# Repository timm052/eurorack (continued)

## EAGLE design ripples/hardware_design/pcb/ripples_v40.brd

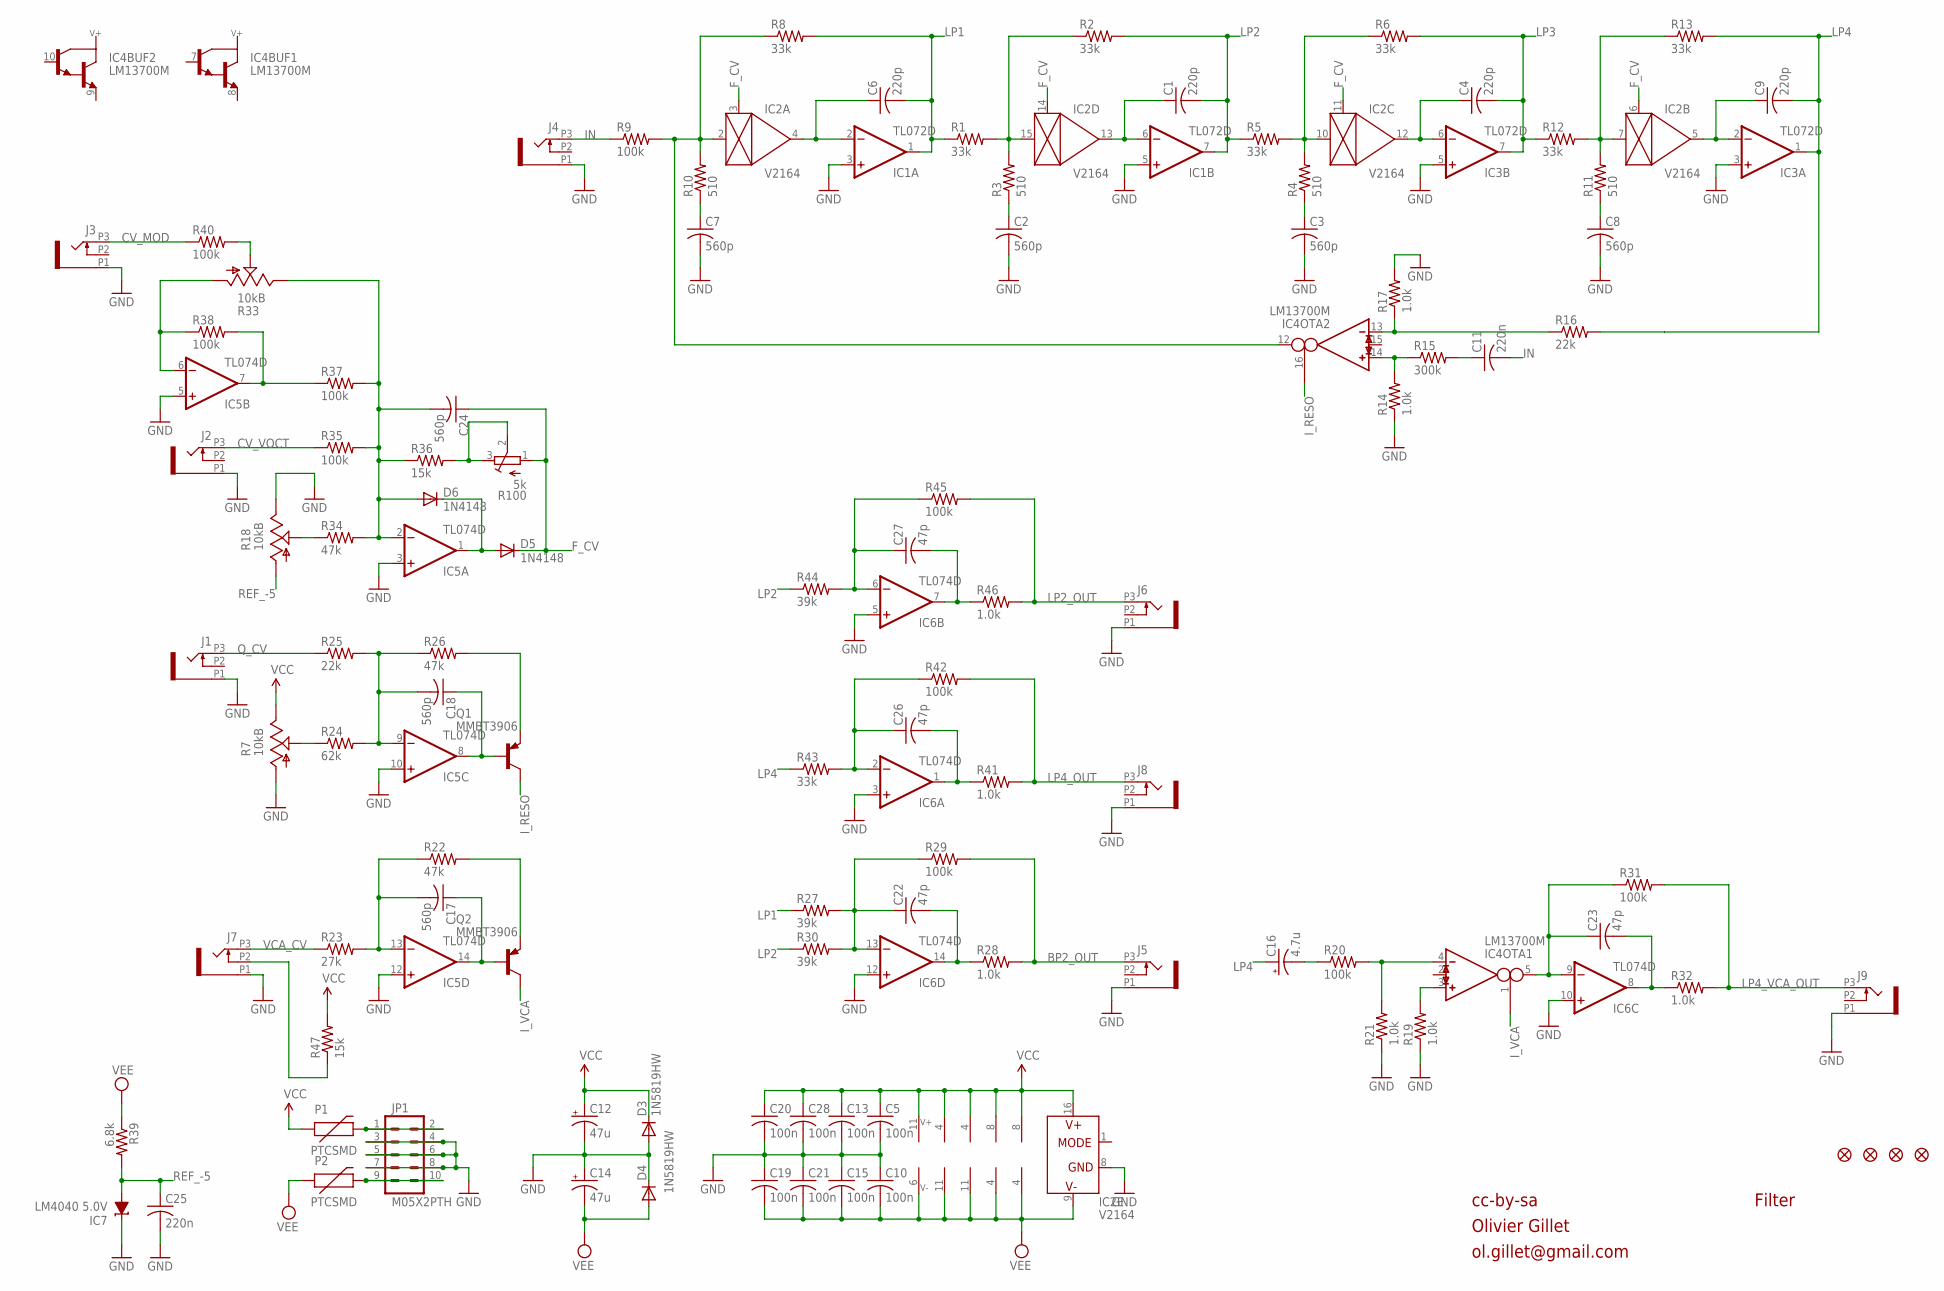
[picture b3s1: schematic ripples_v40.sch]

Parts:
C1, C4, C6, C9: 220p; C0603
C2, C3, C7, C8, C17, C18, C24: 560p; C0603
C5, C10, C13, C15, C19, C20, C21, C28: 100n; C0603
C11, C25: 220n; C0603
C12, C14: 47u; PANASONIC_D
C16: 4.7u; PANASONIC_B
C22, C23, C26, C27: 47p; C0603
D3, D4: 1N5819HW; SOD123
D5, D6: 1N4148; SOD323-W
F1, F2, F3, F4: FIDUCIAL1X2; FIDUCIAL-1X2
IC1, IC3: TL072D; SO08
IC2: V2164; SOIC16N
IC4: LM13700M; SO16
IC5, IC6: TL074D; SO14
IC7: LM4040 5.0V; DBZ_R-PDSO-G3
J1, J2, J3, J4, J5, J6, J7, J8, J9: PJ301_THONKICONN6; WQP_PJ_301M6
JP1: M05X2PTH; AVR_ICSP
P1, P2: PTCSMD; PTC-1206
Q1, Q2: MMBT3906; SOT23-BEC
R1, R2, R5, R6, R8, R12, R13, R43: 33k; R0603
R3, R4, R10, R11: 510; R0603
R7, R18, R33: 10kB; ALPS_POT_VERTICAL_PS
R9, R20, R29, R31, R35, R37, R38, R40, R42, R45: 100k; R0603
R14, R17, R19, R21, R28, R32, R41, R46: 1.0k; R0603
R15: 300k; R0603
R16, R25: 22k; R0603
R22, R26, R34: 47k; R0603
R23: 27k; R0603
R24: 62k; R0603
R27, R30, R44: 39k; R0603
R36, R47: 15k; R0603
R39: 6.8k; R0603
R100: 5k; RTRIM3296X

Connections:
BP2_OUT: J5.P3 (3), R28.2, R29.2
CV_F_POT: R18.P$2 (S), R34.1
CV_MOD: J3.P3 (3), R40.1
CV_VOCT: J2.P3 (3), R35.1
F_CV: C24.1, D5.C, IC2.3 (CTRL), IC2.6 (CTRL), IC2.11 (CTRL), IC2.14 (CTRL), R100.1 (E)
GND: C2.2, C3.2, C5.2, C7.2, C8.2, C10.1, C12.-, C13.2, C14.+, C15.1, C19.1, C20.2, C21.1, C25.2, C28.2, D3.A, D4.C, IC1.3 (+IN), IC1.5 (+IN), IC2.8 (GND), IC3.3 (+IN), IC3.5 (+IN), IC5.3 (+IN), IC5.5 (+IN), IC5.10 (+IN), IC5.12 (+IN), IC6.3 (+IN), IC6.5 (+IN), IC6.10 (+IN), IC6.12 (+IN), IC7.1 (C), J1.P1 (1), J2.P1 (1), J3.P1 (1), J4.P1 (1), J5.P1 (1), J6.P1 (1), J7.P1 (1), J8.P1 (1), J9.P1 (1), JP1.3, JP1.4, JP1.5, JP1.6, JP1.7, JP1.8, R7.P$3 (A), R14.1, R17.2, R18.P$1 (E), R19.1, R21.1
IN: C11.2, J4.P3 (3), R9.1
I_RESO: IC4.16 (I_BIAS), Q1.C
I_VCA: IC4.1 (I_BIAS), Q2.C
LP1: C6.2, IC1.1 (OUT), R1.1, R8.2, R27.1
LP2: C1.2, IC1.7 (OUT), R2.2, R5.1, R30.1, R44.1
LP2_OUT: J6.P3 (3), R45.2, R46.2
LP3: C4.2, IC3.7 (OUT), R6.2, R12.1
LP4: C9.2, C16.+, IC3.1 (OUT), R13.2, R16.2, R43.1
LP4_OUT: J8.P3 (3), R41.2, R42.2
LP4_VCA_OUT: J9.P3 (3), R31.2, R32.2
unnamed: IC5.7 (OUT), R37.1, R38.2
unnamed: C6.1, IC1.2 (-IN), IC2.4 (OUT)
unnamed: IC2.15 (IN), R1.2, R2.1, R3.2
unnamed: R36.2, R100.2 (S), R100.3 (A)
unnamed: IC4.3 (IN_P), R19.2
unnamed: JP1.1, JP1.2, P1.2
unnamed: C11.1, R15.2
unnamed: C7.1, R10.1
unnamed: C1.1, IC1.6 (-IN), IC2.13 (OUT)
unnamed: IC2.2 (IN), IC4.12 (OUT), R8.1, R9.2, R10.2
unnamed: C2.1, R3.1
unnamed: IC2.10 (IN), R4.2, R5.2, R6.1
unnamed: C4.1, IC2.12 (OUT), IC3.6 (-IN)
unnamed: IC4.13 (IN_N), R16.1, R17.1
unnamed: C3.1, R4.1
unnamed: IC2.7 (IN), R11.2, R12.2, R13.1
unnamed: C9.1, IC2.5 (OUT), IC3.2 (-IN)
unnamed: IC4.14 (IN_P), R14.2, R15.1
unnamed: C8.1, R11.1
unnamed: JP1.9, JP1.10, P2.2
unnamed: R33.P$2 (S), R40.2
unnamed: IC5.6 (-IN), R33.P$3 (A), R38.1
unnamed: C24.2, D6.A, IC5.2 (-IN), R33.P$1 (E), R34.2, R35.2, R36.1, R37.2
unnamed: R7.P$2 (S), R24.1
unnamed: C17.2, IC5.13 (-IN), R22.1, R23.2
unnamed: C18.2, IC5.9 (-IN), R24.2, R25.2, R26.1
unnamed: C18.1, IC5.8 (OUT), Q1.B
unnamed: Q1.E, R26.2
unnamed: J7.P2 (2), R47.1
unnamed: C17.1, IC5.14 (OUT), Q2.B
unnamed: Q2.E, R22.2
unnamed: C27.1, IC6.6 (-IN), R44.2, R45.1
unnamed: C26.1, IC6.2 (-IN), R42.1, R43.2
unnamed: C26.2, IC6.1 (OUT), R41.1
unnamed: D5.A, D6.C, IC5.1 (OUT)
unnamed: C27.2, IC6.7 (OUT), R46.1
unnamed: C22.1, IC6.13 (-IN), R27.2, R29.1, R30.2
unnamed: C22.2, IC6.14 (OUT), R28.1
unnamed: IC4.4 (IN_N), R20.2, R21.2
unnamed: C23.1, IC4.5 (OUT), IC6.9 (-IN), R31.1
unnamed: C23.2, IC6.8 (OUT), R32.1
unnamed: C16.-, R20.1
Q_CV: J1.P3 (3), R25.1
REF_-5: C25.1, IC7.2 (A), R18.P$3 (A), R39.2
VCA_CV: J7.P3 (3), R23.1
VCC: C5.1, C12.+, C13.1, C20.1, C28.1, D3.C, IC1.8 (V+), IC2.16 (V+), IC3.8 (V+), IC4.11 (V+), IC5.4 (V+), IC6.4 (V+), P1.1, R7.P$1 (E), R47.2
VEE: C10.2, C14.-, C15.2, C19.2, C21.2, D4.A, IC1.4 (V-), IC2.9 (V-), IC3.4 (V-), IC4.6 (V-), IC5.11 (V-), IC6.11 (V-), P2.1, R39.1

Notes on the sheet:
cc-by-sa
Olivier Gillet
ol.gillet@gmail.com
Filter

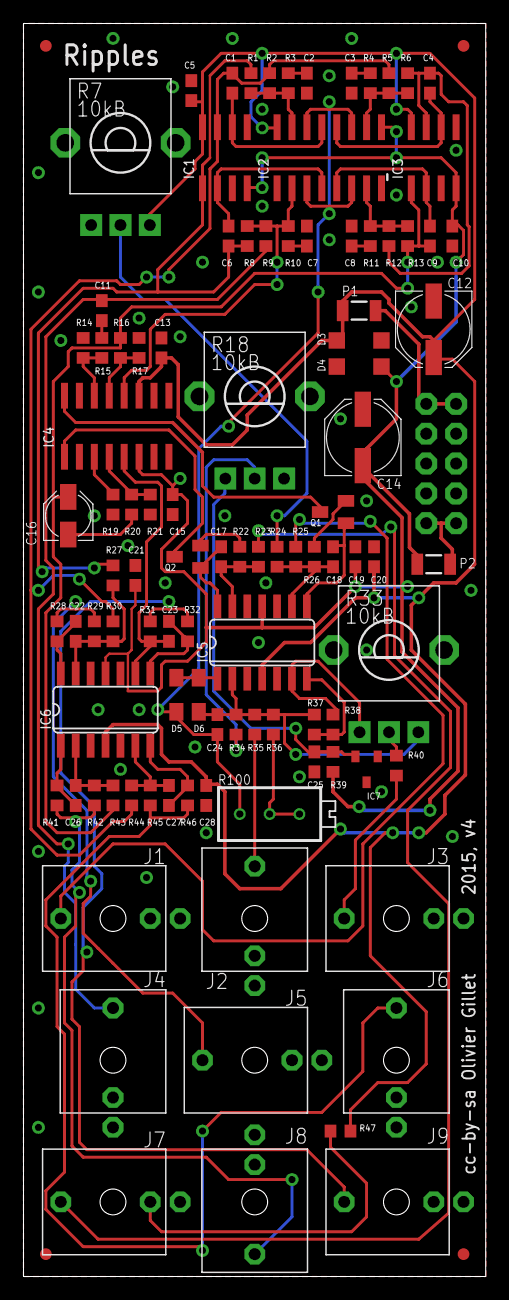
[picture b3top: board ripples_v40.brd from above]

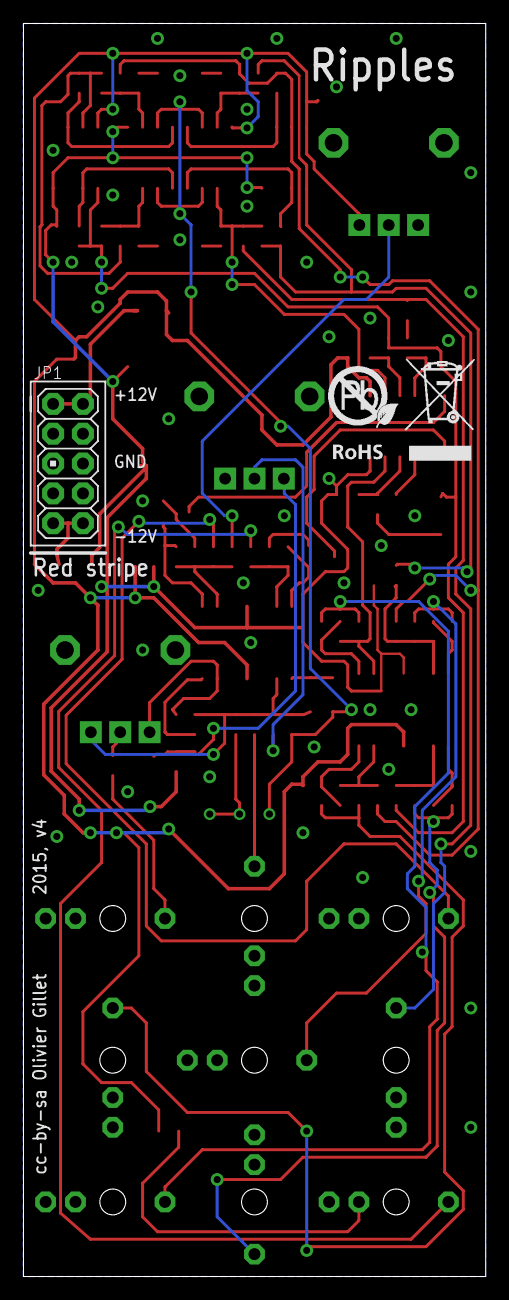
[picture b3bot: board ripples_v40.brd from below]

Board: 2 copper layers, 39.4 x 106.7 mm, 106 parts (2 on the bottom side), 63 nets.

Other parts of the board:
U$2: ROHS

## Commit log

2019-01-21 updated to latest version of eagle
2019-01-27 updates engle file formate ffor bradis and shades
